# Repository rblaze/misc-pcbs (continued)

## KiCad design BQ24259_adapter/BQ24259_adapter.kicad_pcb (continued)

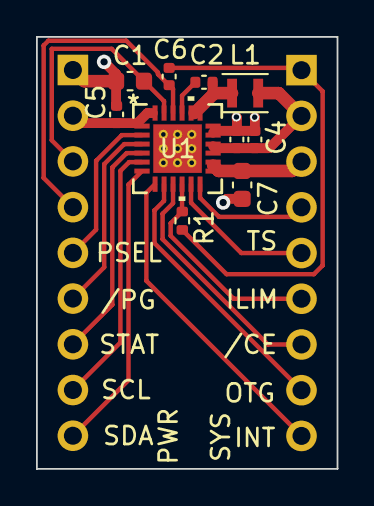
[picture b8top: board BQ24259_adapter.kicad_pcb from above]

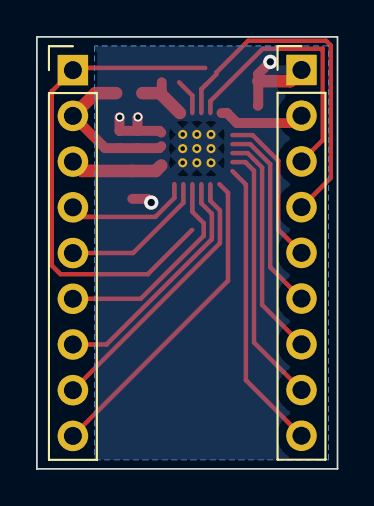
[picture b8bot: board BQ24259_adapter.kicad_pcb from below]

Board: 2 copper layers, 16.7 x 24.0 mm, 12 parts (2 on the bottom side), 20 nets.

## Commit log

2023-10-26 WIP: Breadboard power module using BQ24259
    rblaze/issue_tracker#9
2023-10-27 Add TPS7A20 to libraries
2023-10-27 Schematic drawing for breadboard power module using BQ24259
2023-10-29 Fix small issues in schema
2023-11-01 Partially assigned footprints
2023-11-09 Power board with all components assigned
2023-11-09 Remove power rail connectors
2023-12-02 Routed PCB with a few problems
2024-02-05 Create simplified BQ24259 breakout
2024-02-29 Update to Kicad 8
2024-03-07 Import old STM32 adapter
2024-03-07 Replace STM32 project with STM32L4 breakout
2024-03-12 Finalized breakout for L-series
2024-03-12 Renamed project
2024-03-13 Breakout for STMG0 LQFP48
2024-03-13 Add schema for STM32G0 LQFP32 breakout
2024-03-13 Change IC package from LQFP32 to UFQFPN32
2024-03-14 Finalized G0x1 breakouts
2024-05-18 Add PHR-3 and joystick breakouts
2024-06-01 Minor changes
2024-06-02 Redesign joystick breakout
2024-06-10 Add LCD breakout
2024-07-28 Rotate joystick 45 degrees to get proper axis directions
2024-11-11 Add power module schema
2024-11-11 Remove unused board
2024-11-17 Prepare power module PCB
2025-01-03 Make PG LED green, STAT red
    STAT is usually an error, PG is normal operation.
    Added JLCPCB part numbers for more components.
2025-01-11 Update USB-C connector ID
2025-02-08 Better and smaller Big Red Button
2025-11-16 Add LED adapter
2025-11-23 Add symbol for PAM2804 LED driver
2025-11-23 Update description of PAM2804
2025-11-23 Use high-power LED driver instead of FET
2025-11-23 Replace G0 MCU with C0
2025-11-23 Replace jumper symbols
2025-11-25 Reroute PCB
2025-12-30 Update BOM and CPL settings
2025-12-30 Replace libraries with submodule
2025-12-30 Move Bigger Red Button PCBs to project repo
